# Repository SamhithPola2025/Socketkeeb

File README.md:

# Socketkeeb
Socketkeeb (keyboard) is a custom keyboard I designed in 4 days from PCB to CAD for HackClub's Highway program.
This keyboard was inspired by my need for a keyboard that had low profile switches because those are my favorite type of switches but I could not find a budget one anywhere, so I said why not just make it myself, because that's the solution to most things in life unless its rocket science.

# Challenges
- Designing a PCB compatible with both RP2040 and Kailh Choc switches  
- Sourcing components from multiple vendors while managing shipping costs  
- Ensuring 3D printed keycaps fit properly on low-profile switches  
- Aligning stabilizers and switches without a plate (plateless design quirks)  

# Why I made this
- I wanted a fully custom keyboard with low-profile Choc switches and RP2040 brain  
- I wanted to learn about PCB design, BOM creation, and firmware flashing  
- I like the idea of 3D printing keycaps for a unique personal touch  
- It’s a fun project to build something that’s truly mine from scratch  

# What went good
- Successfully generated a clean BOM and Markdown table for GitHub  
- Found all parts at reasonable prices from trusted vendors  
- 3D printed keycaps turned out better than expected using PLA  
- The design workflow in CAD + PCB tools was smoother than I thought

# BOM: (In BOM.csv too)
| Reference | Quantity | Value | Footprint | Manufacturer | Part Number | Description | Unit Price (USD) | Total Price (USD) | Source Link |
|-----------|----------|--------|------------|--------------|--------------|-------------|------------------|------------------|-------------|
| STAB | 1 set | n/a | PCB Mount | Gateron | n/a | Gateron PCB-mounted stabilizer set (various sizes) | 8.00 | 8.00 | [Gateron](https://www.gateron.com/products/gateron-pcb-mounted-stabilizer?VariantsId=10208) |
| U1 | 1 | RP2040 | Pico W | Raspberry Pi | SC0918 | Raspberry Pi Pico W microcontroller | 7.65 | 7.65 | [DigiKey](https://www.digikey.com/en/products/detail/raspberry-pi/SC0918/16608263) |
| SW1-SW70 | 70 | Kailh Choc Violet | Kailh PG1350 | Kailh | PG1350 | Kailh low-profile Choc Violet switch (70 pcs) | 44.74 | 44.74 | [AliExpress](https://www.aliexpress.us/item/3256806826186563.html) |
| D1-D200 | 200 | 1N4148 | DO-35 | ON Semi | 1N4148 | 1N4148 100V 200mA diode (200 pcs) | 6.76 | 6.76 | [DigiKey](https://www.digikey.com/en/products/detail/onsemi/1N4148/458603) |
| KC1-KC70 | 70 | n/a | n/a | 3D printed | n/a | Custom 3D printed keycaps | 0.00 | 0.00 | n/a |
| **Subtotal** |  |  |  |  |  |  |  | **67.15** |  |
| **Estimated total (with shipping/tax rounded)** |  |  |  |  |  |  |  | **100.00** |  |

# Design Pictures:

# Build Pictures:

## My printer broke down, not enough time for printing legion, have to go to Barcelona tommorow. Decided to 3D print what I could, and I got permission to submit demo form without keycaps. Hope that clears up a few things regarding the demo video!

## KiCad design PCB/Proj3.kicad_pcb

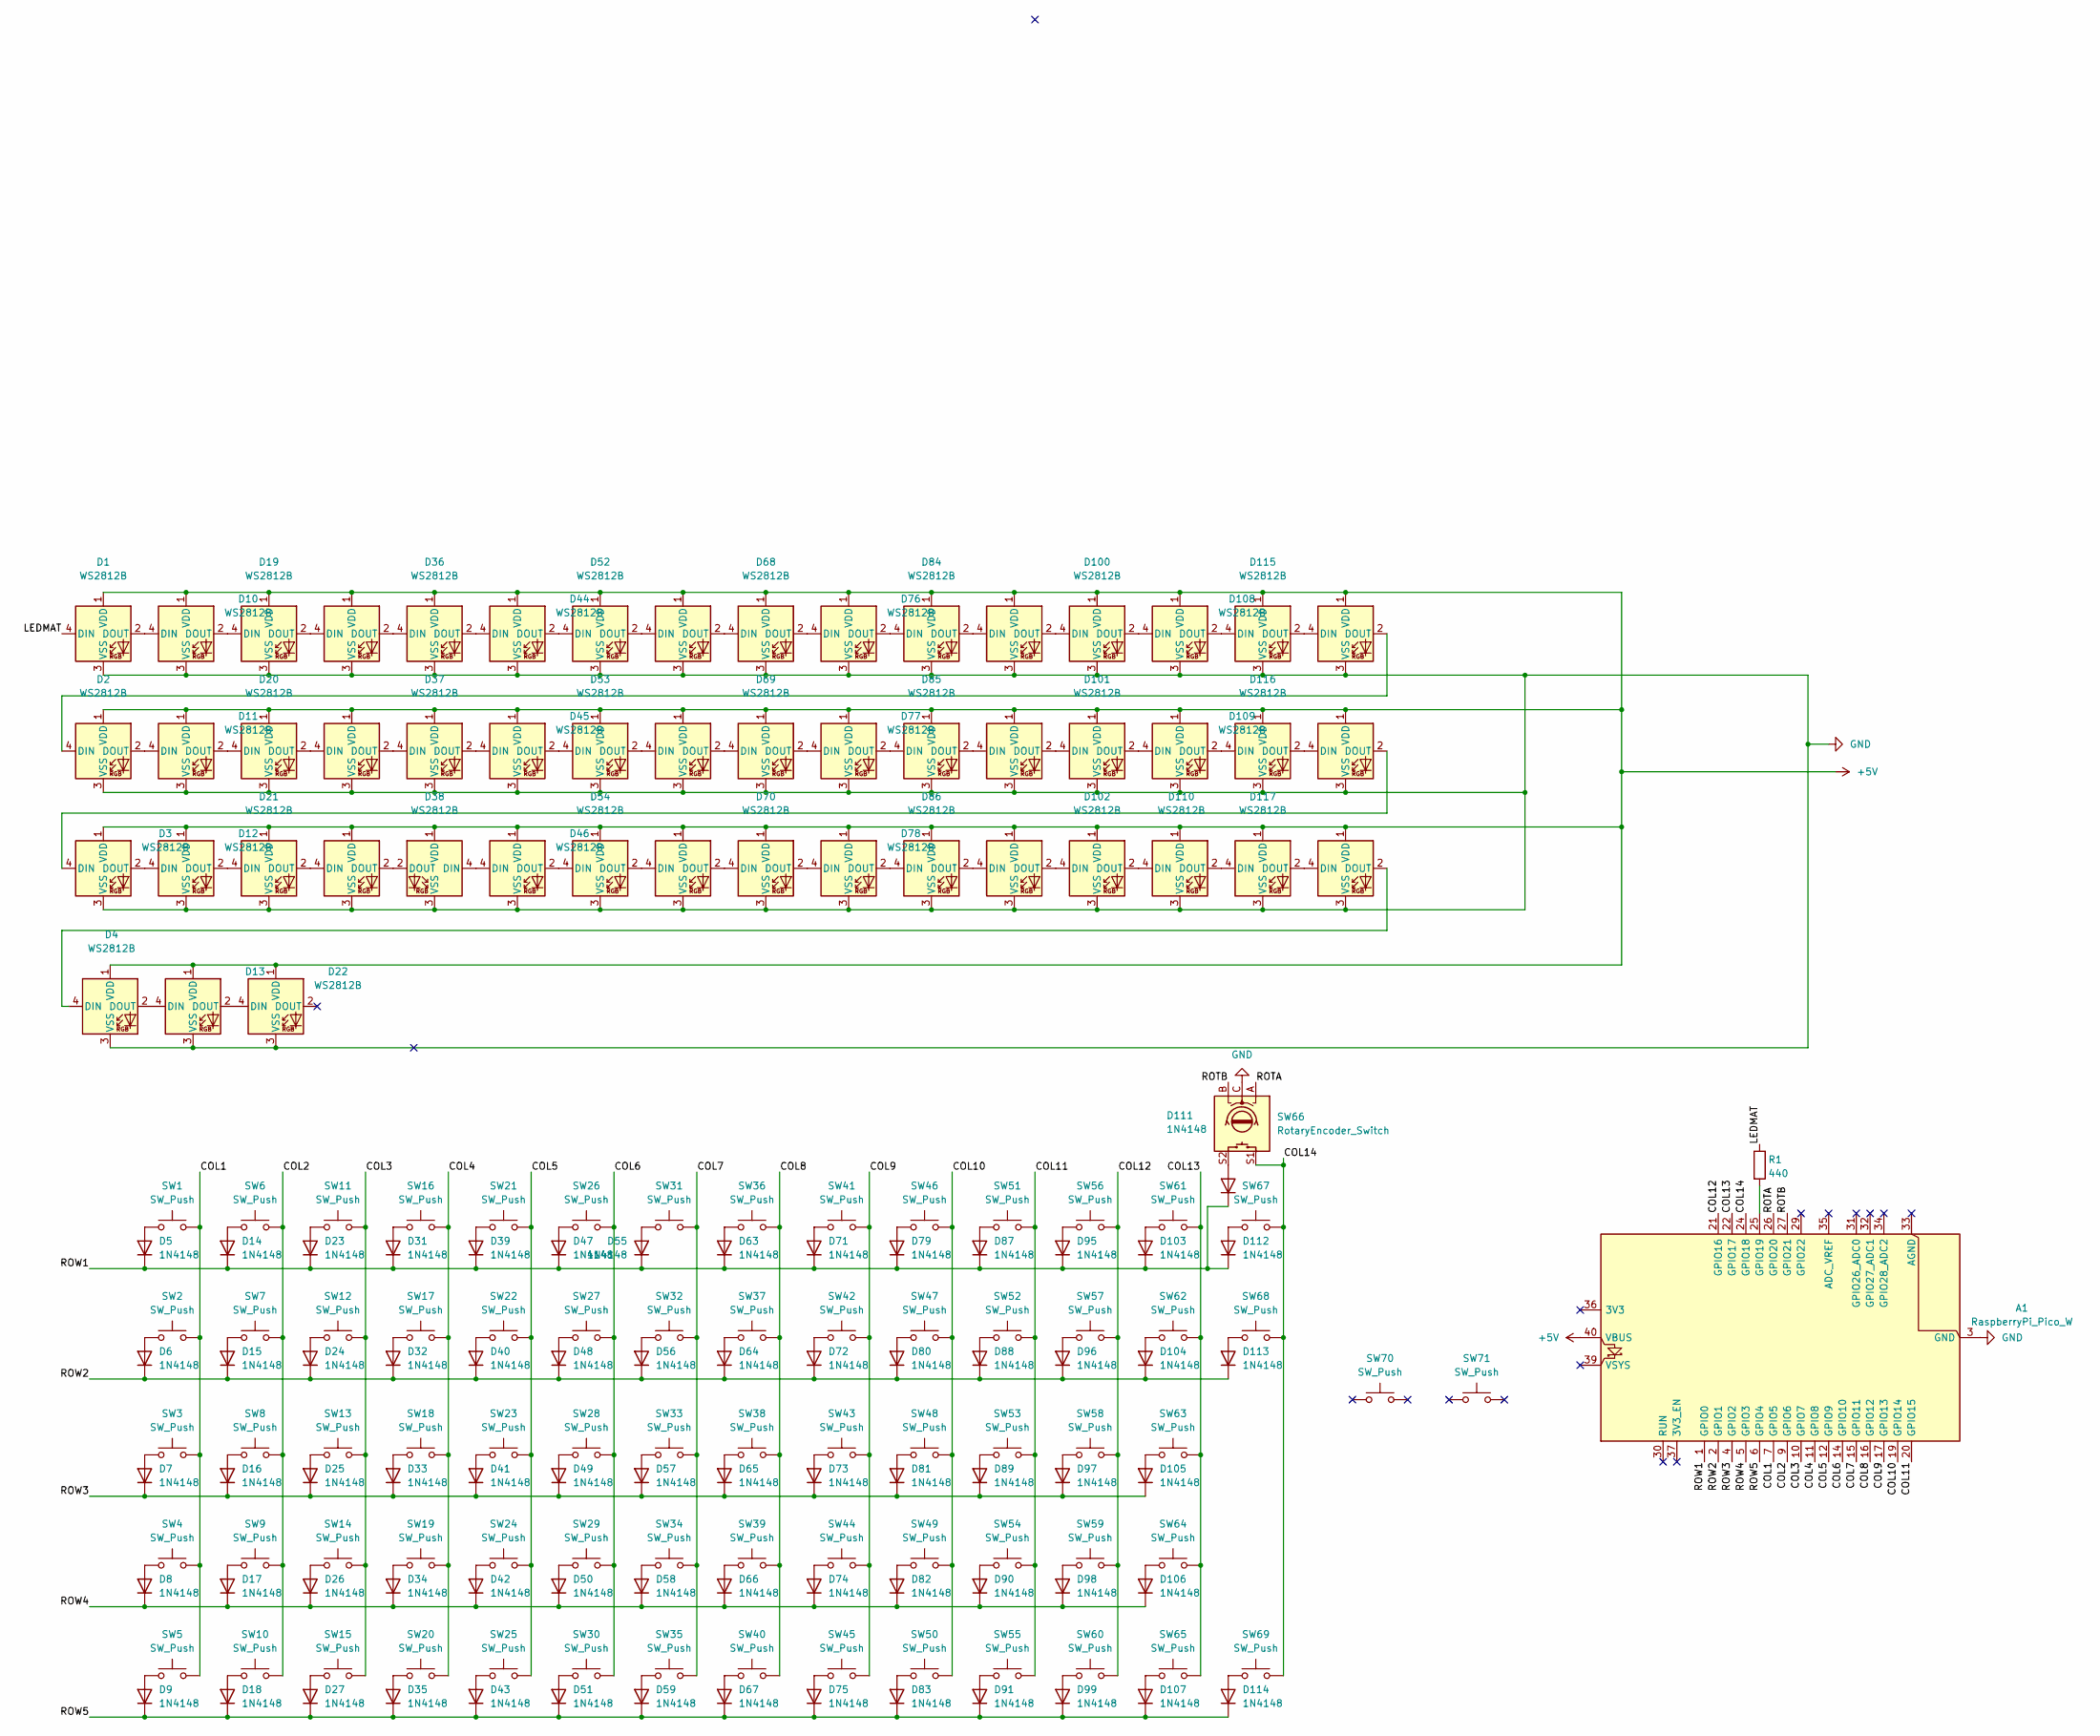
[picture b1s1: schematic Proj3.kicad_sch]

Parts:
A1: RaspberryPi_Pico_W; RaspberryPi_Pico_W_SMD_HandSolder
D1, D2, D3, D4, D10, D11, D12, D13, D19, D20, D21, D22, D28, D29, D30, D36, D37, D38, D44, D45, D46, D52, D53, D54, D60, D61, D62, D68, D69, D70, D76, D77, D78, D84, D85, D86, D92, D93, D94, D100, D101, D102, D108, D109, D110, D115, D116, D117, D118, D119, D120: WS2812B; LED_WS2812B_PLCC4_5.0x5.0mm_P3.2mm
D5, D6, D7, D8, D9, D14, D15, D16, D17, D18, D23, D24, D25, D26, D27, D31, D32, D33, D34, D35, D39, D40, D41, D42, D43, D47, D48, D49, D50, D51, D55, D56, D57, D58, D59, D63, D64, D65, D66, D67, D71, D72, D73, D74, D75, D79, D80, D81, D82, D83, D87, D88, D89, D90, D91, D95, D96, D97, D98, D99, D103, D104, D105, D106, D107, D111, D112, D113, D114: 1N4148; D_DO-35_SOD27_P7.62mm_Horizontal
R1: 440; R_0805_2012Metric
SW1, SW2, SW4, SW5, SW6, SW7, SW9, SW10, SW11, SW12, SW13, SW14, SW15, SW16, SW17, SW18, SW19, SW20, SW21, SW22, SW23, SW24, SW25, SW26, SW27, SW28, SW29, SW30, SW31, SW32, SW33, SW34, SW35, SW36, SW37, SW38, SW39, SW40, SW41, SW42, SW43, SW44, SW45, SW46, SW47, SW48, SW49, SW50, SW51, SW52, SW53, SW54, SW55, SW56, SW57, SW58, SW59, SW60, SW61, SW62, SW63, SW64, SW65, SW67, SW69, SW70, SW71: SW_Push; Kailh-PG1350-1u
SW3: SW_Push; Kailh-PG1350-1.5u
SW8: SW_Push; Kailh-PG1350-1.75u-NoLED
SW66: RotaryEncoder_Switch; RotaryEncoder_Alps_EC11E-Switch_Vertical_H20mm
SW68: SW_Push; Kailh-PG1350-2u

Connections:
+5V: A1.40 (VBUS), D1.1 (VDD), D2.1 (VDD), D3.1 (VDD), D4.1 (VDD), D10.1 (VDD), D11.1 (VDD), D12.1 (VDD), D13.1 (VDD), D19.1 (VDD), D20.1 (VDD), D21.1 (VDD), D22.1 (VDD), D28.1 (VDD), D29.1 (VDD), D30.1 (VDD), D36.1 (VDD), D37.1 (VDD), D38.1 (VDD), D44.1 (VDD), D45.1 (VDD), D46.1 (VDD), D52.1 (VDD), D53.1 (VDD), D54.1 (VDD), D60.1 (VDD), D61.1 (VDD), D62.1 (VDD), D68.1 (VDD), D69.1 (VDD), D70.1 (VDD), D76.1 (VDD), D77.1 (VDD), D78.1 (VDD), D84.1 (VDD), D85.1 (VDD), D86.1 (VDD), D92.1 (VDD), D93.1 (VDD), D94.1 (VDD), D100.1 (VDD), D101.1 (VDD), D102.1 (VDD), D108.1 (VDD), D109.1 (VDD), D110.1 (VDD), D115.1 (VDD), D116.1 (VDD), D117.1 (VDD), D118.1 (VDD), D119.1 (VDD), D120.1 (VDD)
/COL1: A1.7 (GPIO5), SW1.2, SW2.2, SW3.2, SW4.2, SW5.2
/COL2: A1.9 (GPIO6), SW6.2, SW7.2, SW8.2, SW9.2, SW10.2
/COL3: A1.10 (GPIO7), SW11.2, SW12.2, SW13.2, SW14.2, SW15.2
/COL4: A1.11 (GPIO8), SW16.2, SW17.2, SW18.2, SW19.2, SW20.2
/COL5: A1.12 (GPIO9), SW21.2, SW22.2, SW23.2, SW24.2, SW25.2
/COL6: A1.14 (GPIO10), SW26.2, SW27.2, SW28.2, SW29.2, SW30.2
/COL7: A1.15 (GPIO11), SW31.2, SW32.2, SW33.2, SW34.2, SW35.2
/COL8: A1.16 (GPIO12), SW36.2, SW37.2, SW38.2, SW39.2, SW40.2
/COL9: A1.17 (GPIO13), SW41.2, SW42.2, SW43.2, SW44.2, SW45.2
/COL10: A1.19 (GPIO14), SW46.2, SW47.2, SW48.2, SW49.2, SW50.2
/COL11: A1.20 (GPIO15), SW51.2, SW52.2, SW53.2, SW54.2, SW55.2
/COL12: A1.21 (GPIO16), SW56.2, SW57.2, SW58.2, SW59.2, SW60.2
/COL13: A1.22 (GPIO17), SW61.2, SW62.2, SW63.2, SW64.2, SW65.2
/COL14: A1.24 (GPIO18), SW66.S1, SW67.2, SW68.2, SW69.2
/LEDMAT: D1.4 (DIN), R1.1
/ROTA: A1.26 (GPIO20), SW66.A
/ROTB: A1.27 (GPIO21), SW66.B
/ROW1: A1.1 (GPIO0), D5.1 (K), D14.1 (K), D23.1 (K), D31.1 (K), D39.1 (K), D47.1 (K), D55.1 (K), D63.1 (K), D71.1 (K), D79.1 (K), D87.1 (K), D95.1 (K), D103.1 (K), D111.1 (K), D112.1 (K)
/ROW2: A1.2 (GPIO1), D6.1 (K), D15.1 (K), D24.1 (K), D32.1 (K), D40.1 (K), D48.1 (K), D56.1 (K), D64.1 (K), D72.1 (K), D80.1 (K), D88.1 (K), D96.1 (K), D104.1 (K), D113.1 (K)
/ROW3: A1.4 (GPIO2), D7.1 (K), D16.1 (K), D25.1 (K), D33.1 (K), D41.1 (K), D49.1 (K), D57.1 (K), D65.1 (K), D73.1 (K), D81.1 (K), D89.1 (K), D97.1 (K), D105.1 (K)
/ROW4: A1.5 (GPIO3), D8.1 (K), D17.1 (K), D26.1 (K), D34.1 (K), D42.1 (K), D50.1 (K), D58.1 (K), D66.1 (K), D74.1 (K), D82.1 (K), D90.1 (K), D98.1 (K), D106.1 (K)
/ROW5: A1.6 (GPIO4), D9.1 (K), D18.1 (K), D27.1 (K), D35.1 (K), D43.1 (K), D51.1 (K), D59.1 (K), D67.1 (K), D75.1 (K), D83.1 (K), D91.1 (K), D99.1 (K), D107.1 (K), D114.1 (K)
GND: A1.3 (GND), A1.8 (GND), A1.13 (GND), A1.18 (GND), A1.23 (GND), A1.28 (GND), A1.38 (GND), D1.3 (VSS), D2.3 (VSS), D3.3 (VSS), D4.3 (VSS), D10.3 (VSS), D11.3 (VSS), D12.3 (VSS), D13.3 (VSS), D19.3 (VSS), D20.3 (VSS), D21.3 (VSS), D22.3 (VSS), D28.3 (VSS), D29.3 (VSS), D30.3 (VSS), D36.3 (VSS), D37.3 (VSS), D38.3 (VSS), D44.3 (VSS), D45.3 (VSS), D46.3 (VSS), D52.3 (VSS), D53.3 (VSS), D54.3 (VSS), D60.3 (VSS), D61.3 (VSS), D62.3 (VSS), D68.3 (VSS), D69.3 (VSS), D70.3 (VSS), D76.3 (VSS), D77.3 (VSS), D78.3 (VSS), D84.3 (VSS), D85.3 (VSS), D86.3 (VSS), D92.3 (VSS), D93.3 (VSS), D94.3 (VSS), D100.3 (VSS), D101.3 (VSS), D102.3 (VSS), D108.3 (VSS), D109.3 (VSS), D110.3 (VSS), D115.3 (VSS), D116.3 (VSS), D117.3 (VSS), D118.3 (VSS), D119.3 (VSS), D120.3 (VSS), SW66.C
unnamed: A1.25 (GPIO19), R1.2
unnamed: D1.2 (DOUT), D10.4 (DIN)
unnamed: D5.2 (A), SW1.1
unnamed: D6.2 (A), SW2.1
unnamed: D7.2 (A), SW3.1
unnamed: D8.2 (A), SW4.1
unnamed: D9.2 (A), SW5.1
unnamed: D10.2 (DOUT), D19.4 (DIN)
unnamed: D2.2 (DOUT), D11.4 (DIN)
unnamed: D11.2 (DOUT), D20.4 (DIN)
unnamed: D3.2 (DOUT), D12.4 (DIN)
unnamed: D12.2 (DOUT), D21.4 (DIN)
unnamed: D4.2 (DOUT), D13.4 (DIN)
unnamed: D13.2 (DOUT), D22.4 (DIN)
unnamed: D14.2 (A), SW6.1
unnamed: D15.2 (A), SW7.1
unnamed: D16.2 (A), SW8.1
unnamed: D17.2 (A), SW9.1
unnamed: D18.2 (A), SW10.1
unnamed: D19.2 (DOUT), D28.4 (DIN)
unnamed: D20.2 (DOUT), D29.4 (DIN)
unnamed: D21.2 (DOUT), D30.4 (DIN)
unnamed: D23.2 (A), SW11.1
unnamed: D24.2 (A), SW12.1
unnamed: D25.2 (A), SW13.1
unnamed: D26.2 (A), SW14.1
unnamed: D27.2 (A), SW15.1
unnamed: D28.2 (DOUT), D36.4 (DIN)
unnamed: D29.2 (DOUT), D37.4 (DIN)
unnamed: D30.2 (DOUT), D38.2 (DOUT)
unnamed: D31.2 (A), SW16.1
unnamed: D32.2 (A), SW17.1
unnamed: D33.2 (A), SW18.1
unnamed: D34.2 (A), SW19.1
unnamed: D35.2 (A), SW20.1
unnamed: D36.2 (DOUT), D44.4 (DIN)
unnamed: D37.2 (DOUT), D45.4 (DIN)
unnamed: D38.4 (DIN), D46.4 (DIN)
unnamed: D39.2 (A), SW21.1
unnamed: D40.2 (A), SW22.1
unnamed: D41.2 (A), SW23.1
unnamed: D42.2 (A), SW24.1
unnamed: D43.2 (A), SW25.1
unnamed: D44.2 (DOUT), D52.4 (DIN)
unnamed: D45.2 (DOUT), D53.4 (DIN)
unnamed: D46.2 (DOUT), D54.4 (DIN)
unnamed: D47.2 (A), SW26.1
unnamed: D48.2 (A), SW27.1
unnamed: D49.2 (A), SW28.1
unnamed: D50.2 (A), SW29.1
unnamed: D51.2 (A), SW30.1
unnamed: D52.2 (DOUT), D60.4 (DIN)
unnamed: D53.2 (DOUT), D61.4 (DIN)
unnamed: D54.2 (DOUT), D62.4 (DIN)
unnamed: D55.2 (A), SW31.1
unnamed: D56.2 (A), SW32.1
unnamed: D57.2 (A), SW33.1
unnamed: D58.2 (A), SW34.1
unnamed: D59.2 (A), SW35.1
unnamed: D60.2 (DOUT), D68.4 (DIN)
unnamed: D61.2 (DOUT), D69.4 (DIN)
unnamed: D62.2 (DOUT), D70.4 (DIN)
unnamed: D63.2 (A), SW36.1
unnamed: D64.2 (A), SW37.1
unnamed: D65.2 (A), SW38.1
unnamed: D66.2 (A), SW39.1
unnamed: D67.2 (A), SW40.1
unnamed: D68.2 (DOUT), D76.4 (DIN)
unnamed: D69.2 (DOUT), D77.4 (DIN)
unnamed: D70.2 (DOUT), D78.4 (DIN)
unnamed: D71.2 (A), SW41.1
unnamed: D72.2 (A), SW42.1
unnamed: D73.2 (A), SW43.1
unnamed: D74.2 (A), SW44.1
unnamed: D75.2 (A), SW45.1
unnamed: D76.2 (DOUT), D84.4 (DIN)
unnamed: D77.2 (DOUT), D85.4 (DIN)
unnamed: D78.2 (DOUT), D86.4 (DIN)
unnamed: D79.2 (A), SW46.1
unnamed: D80.2 (A), SW47.1
unnamed: D81.2 (A), SW48.1
unnamed: D82.2 (A), SW49.1
unnamed: D83.2 (A), SW50.1
unnamed: D84.2 (DOUT), D92.4 (DIN)
unnamed: D85.2 (DOUT), D93.4 (DIN)
unnamed: D86.2 (DOUT), D94.4 (DIN)
unnamed: D87.2 (A), SW51.1
unnamed: D88.2 (A), SW52.1
unnamed: D89.2 (A), SW53.1
unnamed: D90.2 (A), SW54.1
unnamed: D91.2 (A), SW55.1
unnamed: D95.2 (A), SW56.1
unnamed: D96.2 (A), SW57.1
unnamed: D97.2 (A), SW58.1
unnamed: D98.2 (A), SW59.1
unnamed: D99.2 (A), SW60.1
unnamed: D92.2 (DOUT), D100.4 (DIN)
unnamed: D100.2 (DOUT), D108.4 (DIN)
unnamed: D93.2 (DOUT), D101.4 (DIN)
unnamed: D101.2 (DOUT), D109.4 (DIN)
unnamed: D94.2 (DOUT), D102.4 (DIN)
unnamed: D102.2 (DOUT), D110.4 (DIN)
unnamed: D103.2 (A), SW61.1
unnamed: D104.2 (A), SW62.1
unnamed: D105.2 (A), SW63.1
unnamed: D106.2 (A), SW64.1
unnamed: D107.2 (A), SW65.1
unnamed: D108.2 (DOUT), D115.4 (DIN)
unnamed: D109.2 (DOUT), D116.4 (DIN)
unnamed: D110.2 (DOUT), D117.4 (DIN)
unnamed: D111.2 (A), SW66.S2
unnamed: D112.2 (A), SW67.1
unnamed: D113.2 (A), SW68.1
unnamed: D114.2 (A), SW69.1
unnamed: D115.2 (DOUT), D118.4 (DIN)
unnamed: D116.2 (DOUT), D119.4 (DIN)
unnamed: D117.2 (DOUT), D120.4 (DIN)
unnamed: D2.4 (DIN), D118.2 (DOUT)
unnamed: D3.4 (DIN), D119.2 (DOUT)
unnamed: D4.4 (DIN), D120.2 (DOUT)

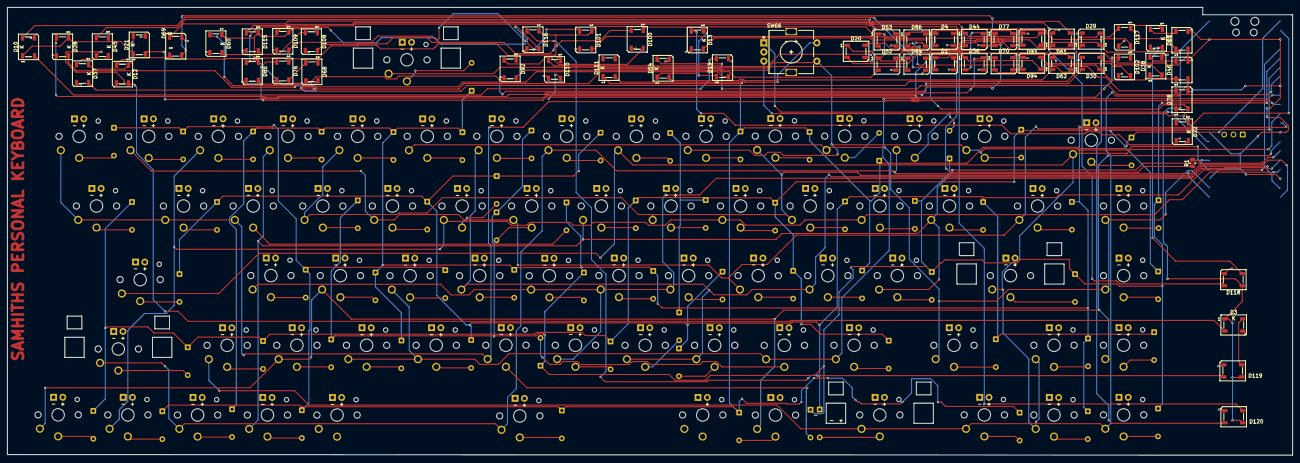
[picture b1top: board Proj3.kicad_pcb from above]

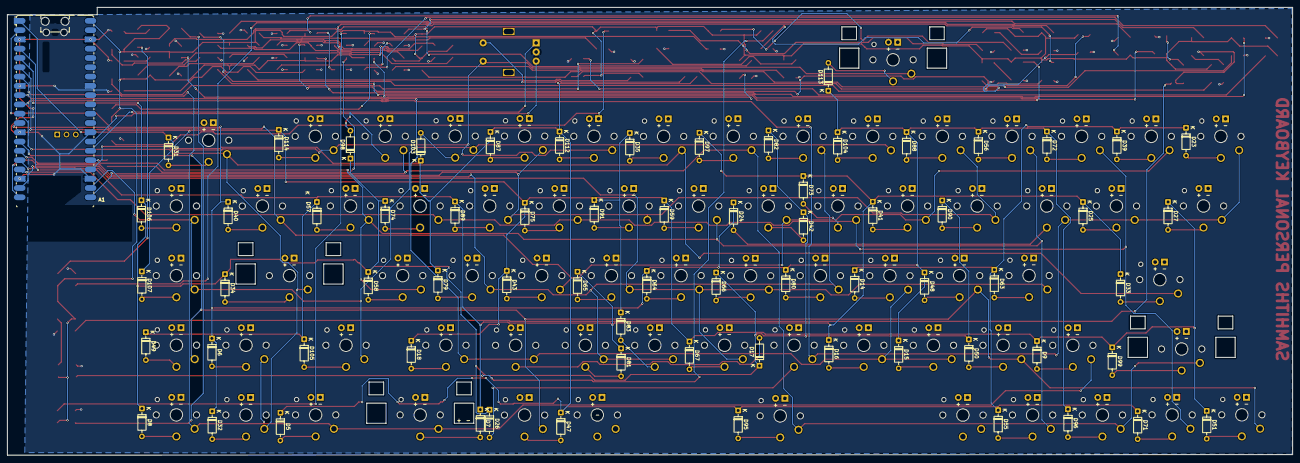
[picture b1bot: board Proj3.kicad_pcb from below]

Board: 2 copper layers, 351.5 x 122.4 mm, 193 parts (69 on the bottom side), 144 nets.

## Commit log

2025-06-28 final commit i think
2025-06-28 finale commit i think
2025-06-28 fixed gerbers
